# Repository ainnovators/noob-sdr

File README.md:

# noob-sdr

An open source SDR board derived from Michael Ossmann's Hackrf project. It should include an onboard FPGA for DSP purposes.

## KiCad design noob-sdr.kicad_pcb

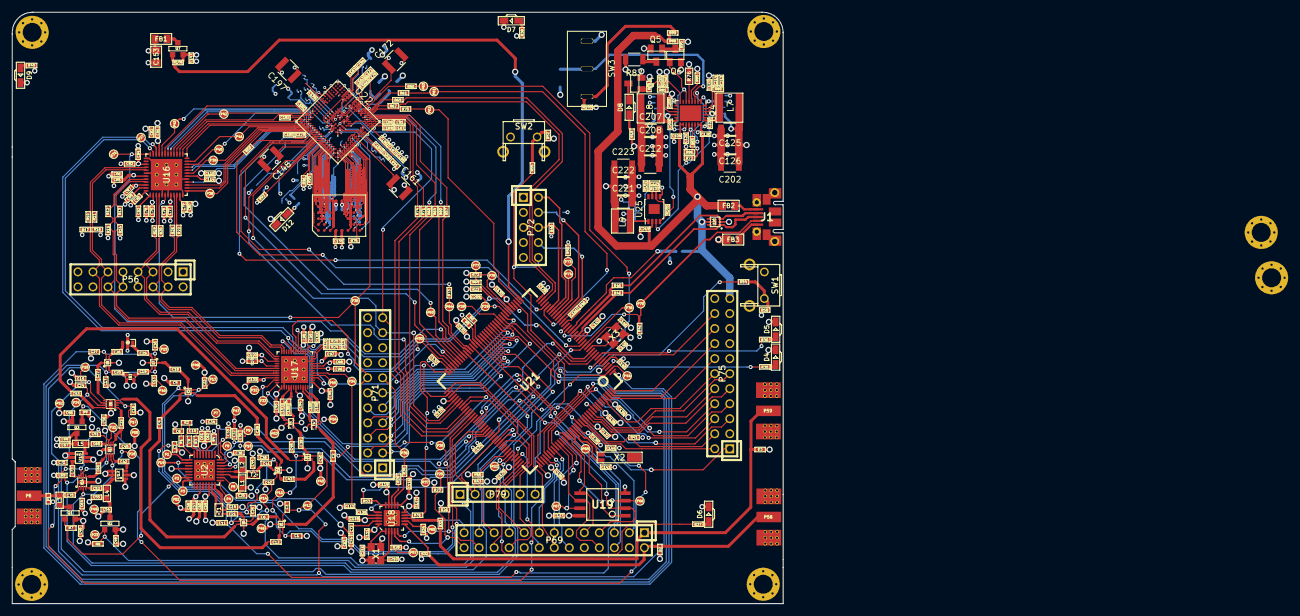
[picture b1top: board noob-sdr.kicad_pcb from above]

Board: 6 copper layers, 130.3 x 100.0 mm, 473 parts (0 on the bottom side), 354 nets.

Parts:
C1, C3, C5, C11, C13, C15, C16, C17, C23, C24, C25, C30, C31, C32, C33, C34, C37, C38, C40, C45, C47, C48, C50, C51, C57, C59, C61, C64, C69, C71, C72, C109: 33pF; 0402
C2, C6, C12, C39, C43, C53, C93, C94, C95, C102, C103, C105: 22pF; 0402
C4, C14, C18, C19, C20, C21, C22, C27, C28, C41, C42, C44, C52, C63, C65, C66, C70, C73, C75, C77, C79, C81, C83, C85, C87, C99, C111, C114, C116, C117, C118, C119, C122, C127, C128, C129, C130, C131, C132, C133, C134, C135, C136, C137, C138, C139, C140, C141, C142, C147, C150, C151, C152, C204: 100nF; 0402
C7, C8: 330pF; 0402
C9: 8p2; 0402
C10, C110, C215: 180pF; 0402
C26, C29, C112: 47pF; 0402
C35, C36, C55, C67, C74, C98, C209: 100pF; 0402
C46, C49, C56, C107, C224: 1uF; 0402
C54, C58, C60, C62, C68, C88, C96, C97, C100, C101, C123: 10nF; 0402
C76, C78, C80, C82, C84, C86, C104, C115, C120, C121, C219: 2.2uF; 0402
C89, C90, C92: 330nF; 0402
C91, C159, C160, C163, C164, C167, C183, C184, C186, C191, C192: 4.7uF; 0402
C106, C108: 3pF; 0402
C113: 3.3nF; 0402
C124, C206: 56pF; 0402
C125, C207: 100uF; C_1206
C126, C148, C178, C185, C198, C208, C222: 47uF; C_1210
C143, C144, C145, C146, C216: 18pF; 0402
C149, C155, C156, C157, C158, C165, C166, C168, C169, C170, C171, C179, C180, C181, C182, C187, C188, C193, C194, C195, C196, C199: 470nF; 0402
C153: 10uF; 0805
C161, C162, C172, C197: 100uF; C_1210
C202, C212, C218, C223: 100nF; C_1210
C203: 13pF; 0402
C205: 22nF; 0402
C210, C211: C; 0402
C213: 470pF; 0402
C214: 62pF; 0402
C217: 160pF; 0402
C220, C225: 6.2pF; 0402
C221: 22uF; C_1206
D1, D2, D3: GSG-DIODE-TVS-BI; 0402
D4: USBLED; LTST-S220
D5: RXLED; LTST-S220
D6: TXLED; LTST-S220
D7: VCCLED; LTST-S220
D8, D12: LED; LTST-S220
D9: VAALED; LTST-S220
FB1, FB2, FB3, FB5: FILTER; 0805
FB4: 600 Ohm/100 MHz; 0805
J1: GSG-USB-MICRO-B-SHIELDED; USB-MICROB-FCI-10103592-EXT
J2, J3, J4, J5, J6, J7: CONN_1; HOLE126MIL-COPPER
L1, L2, L3, L4, L5: 10uH; 0603
L6: 6.2nH; 0402
L7: 1.5uH; NR5040T1R5N
L8: 2.2uH; NR5040T1R5N
L9: 3.3uH; NRS4018T3R3MDGJ
P1, P2, P3, P4, P5, P7, P8, P9, P10, P11, P12, P13, P14, P15, P16, P17, P18, P19, P20, P21, P22, P23, P24, P25, P26, P27, P28, P29, P30, P31, P32, P33, P34, P35, P36, P37, P38, P39, P40, P41, P42, P43, P44, P45, P46, P47, P48, P49, P50, P51, P52, P53, P54, P55, P57, P60, P61, P62, P63, P64, P65, P66, P67, P68, P70, P73, P74, P76, P77, P78: CONN_1; TESTPOINT-50MIL
P6: ANTENNA; GSG-SMA-73251-2120
P56: BASEBAND; HEADER-2x8
P58: CLKIN; GSG-SMA-73251-2120
P59: CLKOUT; GSG-SMA-73251-2120
P69: I2S; HEADER-2x13
P71: GPIO; HEADER-2x11
P72: LPC_JTAG; HEADER-2x5
P75: CONN_11X2; HEADER-2x11
P79: LPC_ISP; HEADER-1x6
Q1, Q2, Q3, Q7: MOSFET_P; SOT23GDS
Q4, Q5, Q6: FDV301N; SOT-23
R1, R2, R35, R38: 470; 0402
R3: 22K; 0402
R4: 51K 1%; 0402
R5, R6, R7, R8, R9, R39, R105: 10K; 0402
R10, R11, R12, R13, R75, R91, R95, R96, R97: 1k 1%; 0402
R14, R15, R16, R17: 4k7 1%; 0402
R18: 680; 0402
R19, R20, R21, R22, R44, R45, R46, R83, R85, R86: 0; 0402
R23, R28, R32, R34, R41, R42, R43, R47, R49, R50, R51, R52, R58, R66, R69, R72, R106: 10k; 0402
R24, R25: 475; 0402
R26, R27, R37, R40: 1k8; 0402
R29, R30, R31, R33, R53, R54, R55, R56, R57, R59, R60, R61, R62, R63, R64, R65, R67, R68, R70, R71, R73, R74: 39; 0402
R36: 1k; 0402
R48: 12k 1%; 0402
R76: 576K; 0603
R77: 100K; 0402
R78: 59K 1%; 0402
R79: 88.7K 1%; 0402
R80: 9.31K 1%; 0402
R81: 32.4K 1%; 0402
R82: 60.4K 1%; 0402
R84: 13.3K 1%; 0402
R87: 100 0.25W; R_1206
R88, R90, R100, R102, R103: 10K 1%; 0402
R89: 4.7K 1%; 0402
R92, R93, R99: 4k7; 0402
R94: 200; 0402
R98: 100; 0402
R101: 619K 1%; 0402
R104: 309K 1%; 0402
SW1: DFU; SWITCH-FSMRA
SW2: RESET; SWITCH-FSMRA
SW3: POWER SWITCH; 500SSP1S1M1QEB
T1: MIX_IN_BALUN; GSG-B0310J50100AHF
T2: MIX_OUT_BALUN; GSG-B0310J50100AHF
T3: RX_BALUN; 2500BL14M100
T4: TX_BALUN; 2500BL14M100
U1, U3, U4, U7, U8, U10, U11: SKY13350; SKY13350-385LF
U2: RFFC5072; GSG-QFN32
U5, U13, U14: SKY13317; SKY13317-373LF
U6: RX_LOWPASS_FILTER; GSG-LP0603
U9: RX_HIGHPASS_FILTER; GSG-HP-DEA
U12, U15: MGA-81563; SOT363
U16: MAX5864; GSG-QFN48-7
U17: MAX2837; GSG-QFN48-6
U18: SI5351C; QFN20-4
U19: W25Q80BV; SOIC8-208
U20: LXES1TBCC2-004; GSG-LXES1TBCC2-004
U21: LPC43XXFBD144; LQFP144
U22: XC7A15T-1CPG236C; BGA_361
U23: IS61WV5128BLL-10BLI; BGA_48
U24: LTC3633; QFN-28-1EP_4x5mm_Pitch0.5mm
U25: LTC3621; MSOP-8-1EP_3x3mm_Pitch0.65mm
X1: GSG-XTAL4PIN; XTAL3.2x2.5mm
X2: RTC_XTAL; XTAL-AB26TRQ
X3: MCU_XTAL; XTAL3.2x2.5mm

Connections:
!MIX_BYPASS: C3.2, C15.2, C40.2, P12.1, U1.1, U5.6, U11.5, U21.50
!RX_AMP_POWER: P24.1, Q3.G, R9.2, U21.106
!TX_AMP_POWER: P23.1, Q2.G, R8.2, U21.97
!VAA_ENABLE: Q7.G, R106.2, U21.37
+1V0: C124.1, C125.1, C126.1, C162.1, C163.1, C164.1, C165.1, C166.1, C198.1, C199.1, C202.1, L7.2, P71.18, R78.2, U22.G10, U22.H10, U22.J10, U22.L10, U22.M10, U22.M11, U22.N10, U22.N11, U24.25
+1V8: C185.1, C186.1, C187.1, C188.1, C220.1, C221.1, C222.1, C223.1, FB4.1, L9.2, R101.2, U22.C9, U22.H13, U22.J13
/baseband/CLK5: C109.2, U18.17
/baseband/COM: C89.1, U16.47
/baseband/CPOUT+: C110.2, R24.2, U17.23
/baseband/CPOUT-: C110.1, R25.2, U17.24
/baseband/IA+: R19.2, U16.3
/baseband/IA-: R20.2, U16.4
/baseband/ID+: R13.1, U16.45
/baseband/ID-: R12.1, U16.44
/baseband/QA+: R22.2, U16.10
/baseband/QA-: R21.2, U16.9
/baseband/QD+: R10.1, U16.40
/baseband/QD-: R11.1, U16.41
/baseband/REFN: C90.2, U16.48
/baseband/RXBBI+: P56.7, R19.1, U17.38
/baseband/RXBBI-: P56.5, R20.1, U17.37
/baseband/RXBBQ+: P56.6, R21.1, U17.36
/baseband/RXBBQ-: P56.4, R22.1, U17.35
/baseband/TXBBI+: P56.12, R12.2, R15.2, U17.43
/baseband/TXBBI-: P56.10, R13.2, R14.2, U17.42
/baseband/TXBBQ+: P56.11, R11.2, R16.2, U17.44
/baseband/TXBBQ-: P56.13, R10.2, R17.2, U17.45
/baseband/XA: C211.2, U18.1, X1.3
/baseband/XB: C210.2, U18.2, X1.1
/baseband/XCVR_CLKOUT: P55.1, U17.16
/baseband/XTAL2: C109.1, C112.2, P34.1, U17.17
/fpga/DONE: R92.1, R98.1, U22.U12
/fpga/INIT: R94.1, U22.U11
/fpga/MODE0: R95.1, U22.V12
/fpga/MODE1: R96.2, U22.W11
/fpga/MODE2: R97.1, U22.U10
/fpga/PROG: R93.1, U22.V10
/fpga/SRAM-A0: U22.V13, U23.A1
/fpga/SRAM-A1: U22.V15, U23.A2
/fpga/SRAM-A2: U22.V17, U23.B2
/fpga/SRAM-A3: U22.W14, U23.A4
/fpga/SRAM-A4: U22.W15, U23.B4
/fpga/SRAM-A5: U22.V16, U23.C4
/fpga/SRAM-A6: U22.W13, U23.A5
/fpga/SRAM-A7: U22.U15, U23.B5
/fpga/SRAM-A8: U22.V14, U23.A6
/fpga/SRAM-A9: U22.K17, U23.H1
/fpga/SRAM-A10: U22.M19, U23.H2
/fpga/SRAM-A11: U22.M18, U23.H3
/fpga/SRAM-A12: U22.R18, U23.H4
/fpga/SRAM-A13: U22.N19, U23.H5
/fpga/SRAM-A14: U22.P18, U23.H6
/fpga/SRAM-A15: U22.T17, U23.G5
/fpga/SRAM-A16: U22.R19, U23.G4
/fpga/SRAM-A17: U22.U17, U23.F4
/fpga/SRAM-A18: U22.V19, U23.F3
/fpga/SRAM-CE: R75.2, U22.P17, U23.G3
/fpga/SRAM-DQ0: U22.U16, U23.B6
/fpga/SRAM-DQ1: U22.W19, U23.C6
/fpga/SRAM-DQ2: U22.U18, U23.F6
/fpga/SRAM-DQ3: U22.T18, U23.G6
/fpga/SRAM-DQ4: U22.W17, U23.B1
/fpga/SRAM-DQ5: U22.W16, U23.C1
/fpga/SRAM-DQ6: U22.U19, U23.F1
/fpga/SRAM-DQ7: U22.N17, U23.G1
/fpga/SRAM-OE: U22.P19, U23.G2
/fpga/SRAM-WE: U22.U14, U23.B3
/mcu/usb/ADC0_0: P75.20, U21.6
/mcu/usb/ADC0_2: P75.16, U21.143
/mcu/usb/ADC0_5: P75.18, U21.144
/mcu/usb/ADC0_6: P75.14, U21.142
/mcu/usb/DBGEN: P73.1, R50.2, U21.28
/mcu/usb/DM: R45.1, U21.20
/mcu/usb/DP: R46.1, U21.18
/mcu/usb/GPIO3_8: P75.5, U21.110
/mcu/usb/GPIO3_9: P75.6, U21.113
/mcu/usb/GPIO3_10: P75.7, U21.115
/mcu/usb/GPIO3_11: P75.8, U21.117
/mcu/usb/GPIO3_12: P75.9, U21.132
/mcu/usb/GPIO3_13: P75.10, U21.133
/mcu/usb/GPIO3_14: P75.11, U21.134
/mcu/usb/GPIO3_15: P75.12, U21.140
/mcu/usb/GP_CLKIN: P76.1, R53.1, U21.14
/mcu/usb/I2C1_SCL: P69.5, U21.88
/mcu/usb/I2C1_SDA: P69.6, U21.87
/mcu/usb/I2S0_RX_MCLK: P69.14, U21.73
/mcu/usb/I2S0_RX_SCK: P69.12, U21.120
/mcu/usb/I2S0_RX_SDA: P69.13, U21.116
/mcu/usb/I2S0_RX_WS: P69.15, U21.114
/mcu/usb/I2S0_TX_MCLK: P69.17, U21.99
/mcu/usb/I2S0_TX_SCK: P69.16, U21.112
/mcu/usb/ISP: P79.2, R43.2, U21.96
/mcu/usb/LED1: R35.1, U21.3
/mcu/usb/LED2: R36.1, U21.8
/mcu/usb/LED3: R37.1, U21.103
/mcu/usb/P1_1: P78.1, R72.1, U21.42
/mcu/usb/P1_2: P77.1, R69.1, U21.43
/mcu/usb/P2_8: P69.23, R54.2, U21.98
/mcu/usb/P2_9: P69.21, R66.1, U21.102
/mcu/usb/P2_13: P69.22, U21.108
/mcu/usb/RESET: P69.3, P72.10, P79.6, R55.2, U21.128
/mcu/usb/RTCX1: C143.1, U21.125, X2.2
/mcu/usb/RTCX2: C144.1, U21.126, X2.1
/mcu/usb/RTC_ALARM: P75.2, U21.129
/mcu/usb/SD_CD: P71.3, U21.60
/mcu/usb/SD_CLK: P71.11, U21.45
/mcu/usb/SD_CMD: P71.9, U21.49
/mcu/usb/SD_DAT0: P71.7, U21.52
/mcu/usb/SD_DAT1: P71.6, U21.53
/mcu/usb/SD_DAT2: P71.5, U21.55
/mcu/usb/SD_DAT3: P71.4, U21.56
/mcu/usb/SD_POW: P71.10, U21.48
/mcu/usb/SD_VOLT0: P71.8, U21.51
/mcu/usb/SGPIO0: P61.1, R61.2, U21.32
/mcu/usb/SGPIO1: R65.2, U21.34
/mcu/usb/SGPIO2: R57.2, U21.62
/mcu/usb/SGPIO3: R60.2, U21.64
/mcu/usb/SGPIO4: R68.2, U21.79
/mcu/usb/SGPIO5: R71.2, U21.83
/mcu/usb/SGPIO6: R74.2, U21.84
/mcu/usb/SGPIO7: P62.1, R70.2, U21.38
/mcu/usb/SGPIO9: P63.1, R56.2, U21.7
/mcu/usb/SGPIO10: P64.1, R73.2, U21.61
/mcu/usb/SGPIO11: P65.1, R62.2, U21.66
/mcu/usb/SGPIO12: R64.2, U21.67
/mcu/usb/SGPIO13: R59.2, U21.15
/mcu/usb/SGPIO14: R63.2, U21.33
/mcu/usb/SGPIO15: R67.2, U21.35
/mcu/usb/SPIFI_CS: P68.1, U19.1, U21.124
/mcu/usb/SPIFI_MISO: P69.7, U19.2, U21.122
/mcu/usb/SPIFI_MOSI: P69.9, U19.5, U21.123
/mcu/usb/SPIFI_SCK: P69.8, U19.6, U21.118
/mcu/usb/SPIFI_SIO2: P66.1, U19.3, U21.121
/mcu/usb/SPIFI_SIO3: P67.1, U19.7, U21.119
/mcu/usb/TCK: P72.4, R51.2, U21.27
/mcu/usb/TDI: P72.8, U21.26
/mcu/usb/TDO: P72.6, R49.2, U21.31
/mcu/usb/TMS: P72.2, U21.30
/mcu/usb/U0_RXD: P69.19, P79.4, U21.81
/mcu/usb/U0_TXD: P69.20, P79.5, U21.75
/mcu/usb/VBAT: C128.2, P75.1, U21.127
/mcu/usb/WAKEUP: P75.4, R41.2, U21.130
/mcu/usb/XTAL1: C145.1, U21.12, X3.1
/mcu/usb/XTAL2: C146.1, U21.13, X3.3
/power/EN: C218.1, SW3.2, U24.3
/power/INT3V3: C121.1, R77.2, R83.2, U24.18, U24.19
/power/PGOOD: Q4.G, R39.1, U24.8
/power/PGOOD1V0: R77.1, U24.1, U25.3
/power/PGOOD1V8: Q6.G, R105.2, U24.6, U25.4
/rf frontend/!ANT_BIAS: P2.1, Q1.G, R7.2, U2.15
/rf frontend/REF_IN: C72.1, C74.2, P19.1, U2.10
/rf frontend/RX_AMP_OUT: C65.1, U13.4
/rf frontend/TX_AMP_IN: C42.1, U13.8
/rf frontend/TX_AMP_OUT: C52.1, U14.4
AMP_BYPASS: C50.1, C69.1, P22.1, U13.6, U14.6, U21.104
CLK6: P69.25, U18.16
CLKIN: D2.2, P58.1, P69.2, R32.1, U18.6
CLKOUT: D3.2, P59.1, P69.1, R33.1
CS_AD: P31.1, U16.36, U21.65
CS_XCVR: P30.1, U17.30, U21.70
DA0: P38.1, U16.13, U22.W5
DA1: U16.14, U22.V5
DA2: U16.15, U22.W4
DA3: U16.16, U22.U5
DA4: P39.1, U16.19, U22.V4
DA5: U16.20, U22.U4
DA6: U16.21, U22.U2
DA7: P40.1, U16.22, U22.U3
DD0: P41.1, U16.23, U22.W3
DD1: U16.24, U22.V3
DD2: U16.25, U22.W2
DD3: U16.26, U22.V2
DD4: U16.27, U22.U1
DD5: P42.1, U16.28, U22.T1
DD6: U16.29, U22.T3
DD7: U16.30, U22.R3
DD8: U16.31, U22.T2
DD9: P43.1, U16.32, U22.R2
FPGA_TCK: P71.21, U21.74, U22.C8
FPGA_TDI: P71.19, U21.78, U22.W10
FPGA_TDO: U21.69, U22.W8
FPGA_TMS: U21.82, U22.W9
GCK1: P35.1, P71.14, R29.1, U16.6, U22.L17
GCK2: P36.1, P71.13, R30.1
GND: C1.1, C3.1, C5.2, C7.1, C8.1, C11.1, C13.2, C14.1, C15.1, C16.1, C17.2, C23.1, C24.1, C25.1, C30.2, C31.1, C32.1, C33.1, C34.1, C35.1, C36.1, C37.2, C38.1, C40.1, C44.1, C45.2, C46.2, C47.1, C48.1, C49.2, C50.2, C51.2, C54.2, C55.2, C56.2, C57.1, C58.1, C59.1, C60.1, C61.1, C62.1, C63.1, C64.2, C67.2, C68.2, C69.2, C71.2, C74.1, C75.2, C76.2, C77.2, C78.2, C79.2, C80.2, C81.2, C82.2, C83.2, C84.2, C85.2, C86.2, C87.2, C88.2, C89.2, C90.1, C91.2, C92.1, C93.2, C94.2, C95.2, C96.2, C97.2, C98.2, C99.2, C100.2, C101.2, C102.2, C104.2, C107.2, C111.1, C112.1, C114.2, C115.2, C116.2, C117.2, C118.2, C119.2, C120.2, C121.2, C123.1, C125.2, C126.2, C127.2, C128.1, C129.2, C130.2, C131.2, C132.2, C133.2, C134.2, C135.2, C136.2, C137.2, C138.2, C139.2, C140.2, C141.2, C142.2, C143.2, C144.2, C145.2, C146.2, C147.2, C148.2, C151.2, C152.2, C153.2, C155.2, C156.2, C157.2, C158.2, C159.2, C160.2, C161.2, C162.2, C163.2, C164.2, C165.2, C166.2, C167.2, C168.2, C169.2, C170.2, C171.2, C172.2, C178.2, C179.2, C180.2, C181.2, C182.2, C183.2, C184.2, C185.2, C186.2, C187.2, C188.2, C191.2, C192.2, C193.2, C194.2, C195.2, C196.2, C197.2, C198.2, C199.2, C202.2, C203.2, C205.1, C207.2, C208.2, C209.1, C210.1, C211.1, C212.2, C213.2, C214.2, C215.2, C216.2, C217.2, C218.2, C219.2, C221.2, C222.2, C223.2, C225.2, D1.2, D2.1, D3.1, D4.1, D5.1, D6.1, D7.1, D9.1, D12.1, FB3.2, FB5.2, J1.0, J2.1, J3.1, J4.1, J5.1, J6.1, J7.1, P6.2, P45.1, P46.1, P47.1, P48.1, P49.1, P50.1, P51.1, P52.1, P53.1, P54.1, P56.1, P56.2, P56.3, P56.8, P56.9, P56.14, P56.15, P56.16, P58.2, P59.2, P69.4, P69.10, P69.18, P71.2, P71.12, P71.22, P72.3, P72.5, P72.9, P75.13, P75.15, P75.19, P79.1, Q4.S, Q5.S, Q6.S, R4.1, R14.1, R15.1, R16.1, R17.1, R23.1, R32.2, R47.1, R48.2, R58.1, R66.2, R69.2, R72.2, R76.2, R79.1, R84.1, R85.1, R86.1, R90.1, R96.1, R100.1, R104.1, SW1.0, SW2.0, SW2.2, SW3.3, T3.2, T3.5, T4.2, T4.5, U1.3, U2.0, U2.12, U3.3, U4.3, U5.0, U6.2, U6.3, U7.3, U8.3, U9.2, U9.4, U10.3, U11.3, U12.1, U12.2, U12.4, U12.5, U13.0, U14.0, U15.1, U15.2, U15.4, U15.5, U16.0, U16.5, U16.7, U16.12, U16.17, U16.37, U16.42, U17.0, U17.2, U17.22, U17.26, U18.0, U19.4, U20.2, U21.4, U21.19, U21.23, U21.40, U21.76, U21.109, U21.135, U22.A1, U22.A3, U22.A5, U22.A7, U22.A9, U22.A11, U22.A19, U22.B1, U22.B3, U22.B5, U22.B7, U22.B9, U22.B11, U22.B14, U22.C1, U22.C2, U22.C3, U22.C4, U22.C5, U22.C6, U22.C10, U22.C19, U22.D3, U22.E1, U22.E2, U22.E3, U22.E17, U22.F1, U22.F2, U22.F3, U22.F19, U22.G1, U22.G7, U22.G8, U22.G9, U22.G11, U22.H7, U22.H8, U22.H9, U22.H11, U22.H12, U22.H18, U22.J8, U22.J9, U22.J11, U22.J12, U22.K8, U22.L8, U22.L9, U22.L11, U22.L19, U22.M9, U22.M13, U22.N9, U22.N12, U22.N13, U22.P2, U22.T19, U22.U6, U22.U9, U22.V18, U22.W1, U22.W12, U23.D1, U23.E6, U24.7, U24.29, U25.8, U25.9, X1.2, X1.4, X3.2, X3.4
HOST_CAPTURE: R56.1, U22.A14
HOST_DATA0: R61.1, U22.A15
HOST_DATA1: R65.1, U22.B15
HOST_DATA2: R57.1, U22.A17
HOST_DATA3: R60.1, U22.C15
HOST_DATA4: R68.1, U22.C16
HOST_DATA5: R71.1, U22.A18
HOST_DATA6: R74.1, U22.B18
HOST_DATA7: R70.1, U22.B16
HOST_DECIM_SEL0: R59.1, U22.V7
HOST_DECIM_SEL1: R63.1, U22.U7
HOST_DECIM_SEL2: R67.1, U22.A16
HOST_DIRECTION: R62.1, U22.U8
HOST_DISABLE: R73.1, U22.V8
HOST_Q_INVERT: R64.1, U22.C17
HP: C30.1, C37.1, P15.1, U7.1, U8.5, U21.1
LP: C13.1, C17.1, P16.1, U7.5, U8.1, U21.39
MCU_CLK: R53.2, U18.15
MIXER_ENX: C32.2, P9.1, R6.1, U2.30, U21.57
MIXER_RESETX: C31.2, P10.1, R5.1, U2.29, U21.58
MIXER_SCLK: C33.2, P8.1, U2.31, U21.95
MIXER_SDATA: C34.2, P7.1, U2.32, U21.80
MIX_BYPASS: C1.2, C48.2, P11.1, U1.5, U11.1, U21.86
MIX_CLK: C72.2, U18.19
unnamed: C2.1, U1.6
unnamed: C4.1, U3.2
unnamed: C4.2, U4.2
unnamed: C6.1, U4.4
unnamed: C6.2, U1.2
unnamed: C7.2, R1.2, U2.8
unnamed: C8.2, R1.1, R2.2
unnamed: C9.1, R3.2, U2.6
unnamed: C10.1, R3.1
unnamed: C9.2, C10.2, R2.1, U2.7
unnamed: C12.1, U5.4
unnamed: C12.2, U1.4
unnamed: C14.2, T1.2
unnamed: C18.1, U3.6
unnamed: C18.2, U7.6
unnamed: C19.1, U7.4
unnamed: C19.2, U6.4
unnamed: C20.1, U6.1
unnamed: C20.2, U8.2
unnamed: C21.1, T1.1
unnamed: C21.2, U4.6
unnamed: C22.1, U13.1
unnamed: C22.2, U5.1
unnamed: C26.1, U8.4
unnamed: C26.2, U9.3
unnamed: C27.1, U8.6
unnamed: C27.2, U5.5
unnamed: C28.1, U10.4
unnamed: C28.2, U3.4
unnamed: C29.1, U9.1
unnamed: C29.2, U7.2
unnamed: C39.1, U11.6
unnamed: C41.1, T2.1
unnamed: C41.2, U10.6
unnamed: C42.2, U12.3
unnamed: C43.1, U11.4
unnamed: C43.2, U10.2
unnamed: C44.2, T2.2
unnamed: C52.2, L4.2, U12.6
unnamed: C53.1, U11.2
unnamed: C53.2, U5.8
unnamed: C54.1, C55.1, L4.1, Q2.D
unnamed: C65.2, L5.1, U15.6
unnamed: C66.1, U13.5
unnamed: C66.2, U14.5
unnamed: C67.1, C68.1, L5.2, Q3.D
unnamed: C70.1, D1.1, L3.2, P6.1
unnamed: C70.2, U14.1
unnamed: C73.1, U15.3
unnamed: C73.2, U14.8
unnamed: C92.2, U16.1
unnamed: C103.1, L6.1, U17.4
unnamed: C103.2, T3.4
unnamed: C105.1, L6.2, U17.5
unnamed: C105.2, T3.3
unnamed: C106.1, U17.10
unnamed: C106.2, T4.4
unnamed: C107.1, U17.27
unnamed: C108.1, U17.11
unnamed: C108.2, T4.3
unnamed: C113.1, R25.1
unnamed: C113.2, R24.1
unnamed: C122.1, L7.1, U24.23, U24.24
unnamed: C122.2, U24.20
unnamed: C123.2, U24.27
unnamed: C124.2, C203.1, R78.1, R79.2, U24.28
unnamed: C149.1, C150.1, FB4.2, U22.C13
unnamed: C204.1, L8.1, U24.13, U24.14
unnamed: C204.2, U24.17
unnamed: C205.2, U24.10
unnamed: C206.2, C217.1, R82.1, R84.2, U24.9
unnamed: C213.1, R80.1
unnamed: C214.1, R80.2, U24.26
unnamed: C215.1, R81.1
unnamed: C216.1, R81.2, U24.11
unnamed: C220.2, C225.1, R101.1, R104.2, U25.5
unnamed: C224.1, R102.1
unnamed: C224.2, R103.1, R105.1, U25.6
unnamed: D4.2, R35.2
unnamed: D5.2, R36.2
unnamed: D6.2, R37.2
unnamed: D7.2, R38.2
unnamed: D8.1, Q4.D
unnamed: D8.2, R18.1
unnamed: D9.2, R40.2
unnamed: D12.2, R98.2
unnamed: FB1.1, Q7.D
unnamed: FB2.1, J1.1
unnamed: FB3.1, J1.5
unnamed: J1.2, R45.2, U20.3
unnamed: J1.3, R46.2, U20.1
unnamed: J1.4, P70.1, R42.1, U21.22
unnamed: L1.2, T2.4, U2.27
unnamed: L2.2, T2.3, U2.28
unnamed: L3.1, Q1.D
unnamed: L9.1, U25.1
unnamed: P1.1, U2.9
unnamed: P3.1, U2.16
unnamed: P4.1, U2.25
unnamed: P5.1, U2.26
unnamed: P57.1, R28.2, U18.3
unnamed: P60.1, R34.2, U18.7
unnamed: P74.1, U21.29
unnamed: Q5.D, R87.1
unnamed: Q5.G, Q6.D, R88.1, R90.2
unnamed: R4.2, U2.4
unnamed: R29.2, U18.13
unnamed: R30.2, U18.12
unnamed: R31.2, U18.9
unnamed: R33.2, U18.8
unnamed: R44.1, R47.2, U21.21
unnamed: R48.1, U21.24
unnamed: R52.1, R55.1, SW2.1
unnamed: R54.1, R58.2, SW1.1
unnamed: R76.1, U24.5
unnamed: R83.1, R86.2, U24.2
unnamed: R85.2, U24.4
unnamed: R91.1, U22.E18
unnamed: R99.2, U22.V11
unnamed: R89.1, R100.2, SW3.1
unnamed: R102.2, R103.2, U25.7
unnamed: T1.3, U2.24
unnamed: T1.4, U2.23
RSSI: P44.1, U17.32, U21.2
RX: C5.1, C11.2, C47.2, P14.1, U3.1, U4.1, U10.1, U21.91
RXENABLE: P33.1, U17.48, U21.10
RX_AMP: C51.1, C71.1, P21.1, U13.3, U14.7, U21.105
RX_IF: C39.2, T3.1
RX_MIX_BP: C24.2, P18.1, U5.7, U21.54
SCL: P25.1, P69.26, R27.2, U18.4, U21.92
SDA: P26.1, P69.24, R26.2, U18.5, U21.93
SGPIO_CLK: P37.1, R31.1, U21.72
SSP1_MISO: C209.2, P29.1, U17.29, U21.44
SSP1_MOSI: P28.1, U16.34, U17.31, U21.47
SSP1_SCK: P27.1, U16.35, U17.15, U21.68
TX: C23.2, C25.2, C38.2, P13.1, U3.5, U4.5, U10.5, U21.85
TXENABLE: P32.1, U17.47, U21.9
TX_AMP: C45.1, C64.1, P20.1, U13.7, U14.3, U21.63
TX_IF: C2.2, T4.1
TX_MIX_BP: C16.2, P17.1, U5.3, U21.46
VAA: C35.2, C36.2, C46.1, C49.1, C56.1, C59.2, C60.2, C61.2, C62.2, C63.2, C75.1, C76.1, C77.1, C78.1, C79.1, C80.1, C81.1, C82.1, C83.1, C84.1, C85.1, C86.1, C87.1, C93.1, C94.1, C95.1, C96.1, C97.1, C98.1, C99.1, C100.1, C101.1, C102.1, C153.1, FB1.2, L1.1, L2.1, Q1.S, Q2.S, Q3.S, R7.1, R8.1, R9.1, R40.1, U2.5, U2.22, U16.2, U16.8, U16.11, U16.33, U16.39, U16.43, U16.46, U17.1, U17.7, U17.13, U17.19, U17.21, U17.28, U17.39, U17.41, U17.46
VBUS: C104.1, C120.1, C219.1, FB2.2, P75.21, R44.2, R88.2, R89.2, U20.5, U24.15, U24.16, U24.21, U24.22, U25.2
VCC: C57.2, C58.2, C88.1, C91.1, C111.2, C114.1, C115.1, C116.1, C117.1, C118.1, C119.1, C127.1, C129.1, C130.1, C131.1, C132.1, C133.1, C134.1, C135.1, C136.1, C137.1, C138.1, C139.1, C140.1, C141.1, C142.1, C147.1, C148.1, C151.1, C152.1, C155.1, C156.1, C157.1, C158.1, C159.1, C160.1, C161.1, C167.1, C168.1, C169.1, C170.1, C171.1, C172.1, C178.1, C179.1, C180.1, C181.1, C182.1, C183.1, C184.1, C191.1, C192.1, C193.1, C194.1, C195.1, C196.1, C197.1, C206.1, C207.1, C208.1, C212.1, L8.2, P69.11, P71.1, P72.1, P75.3, Q7.S, R5.2, R6.2, R18.2, R26.1, R27.1, R28.1, R34.1, R38.1, R39.2, R41.1, R42.2, R43.1, R49.1, R50.1, R51.1, R52.2, R75.1, R82.2, R87.2, R91.2, R92.2, R93.2, R94.2, R95.2, R97.2, R99.1, R106.1, SW1.2, U2.19, U16.18, U17.20, U18.10, U18.11, U18.14, U18.18, U18.20, U19.8, U21.5, U21.16, U21.17, U21.25, U21.36, U21.41, U21.59, U21.71, U21.77, U21.94, U21.107, U21.111, U21.131, U21.137, U21.141, U22.B19, U22.C14, U22.C18, U22.F17, U22.G12, U22.G13, U22.H3, U22.J7, U22.K1, U22.K7, U22.K12, U22.K13, U22.L7, U22.L12, U22.L13, U22.M7, U22.M8, U22.M12, U22.M17, U22.N7, U22.N8, U22.R1, U22.R17, U22.U13, U22.V1, U22.V6, U22.V9, U23.D6, U23.E1, U24.12
XADCGND: C149.2, C150.2, FB5.1, U22.A12, U22.A13, U22.B12, U22.B13, U22.C12
XCVR_EN: R23.2, U17.25, U21.11

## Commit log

2016-11-18 Update README.md
    Description
2016-11-19 Add files via upload
    first upload
2016-11-22 Add files via upload
    Replaced FPGA's configuring Flash, since LPC4320 configures CPLD in original design
2017-02-07 Add files via upload
    Changed power distribution system, increased board size
2017-03-02 Add files via upload
    Noob-sdr v1.0
